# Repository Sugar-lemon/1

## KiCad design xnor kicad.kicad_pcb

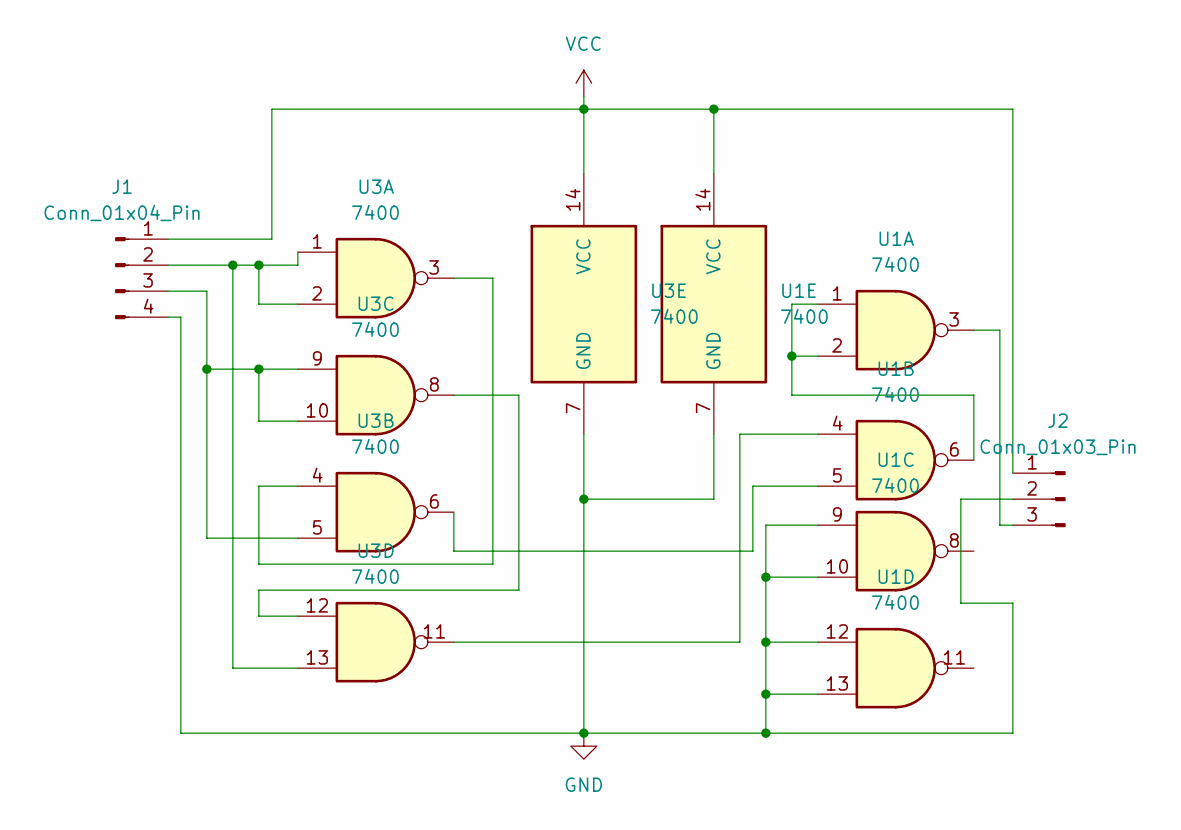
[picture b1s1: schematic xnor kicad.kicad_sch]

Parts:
J1: Conn_01x04_Pin
J2: Conn_01x03_Pin
U1, U3: 7400; DIP-14_W7.62mm

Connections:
GND: J1.4, J2.2, U1.7 (GND), U1.9, U1.10, U1.12, U1.13, U3.7 (GND)
unnamed: J1.2, U3.1, U3.2, U3.13
unnamed: J1.3, U3.5, U3.9, U3.10
unnamed: J2.3, U1.3
unnamed: U1.1, U1.2, U1.6
unnamed: U1.4, U3.11
unnamed: U1.5, U3.6
unnamed: U3.3, U3.4
unnamed: U3.8, U3.12
VCC: J1.1, J2.1, U1.14 (VCC), U3.14 (VCC)

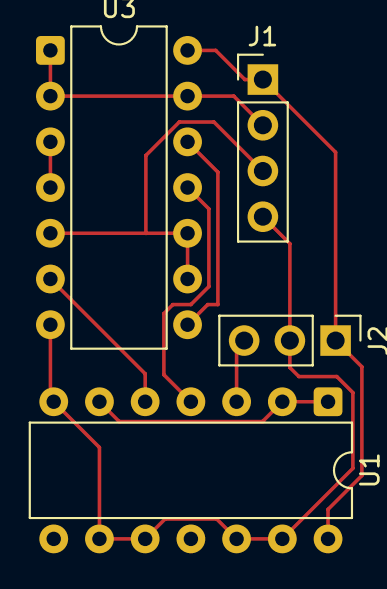
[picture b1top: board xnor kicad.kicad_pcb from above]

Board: 2 copper layers, 4 parts (0 on the bottom side), 10 nets.

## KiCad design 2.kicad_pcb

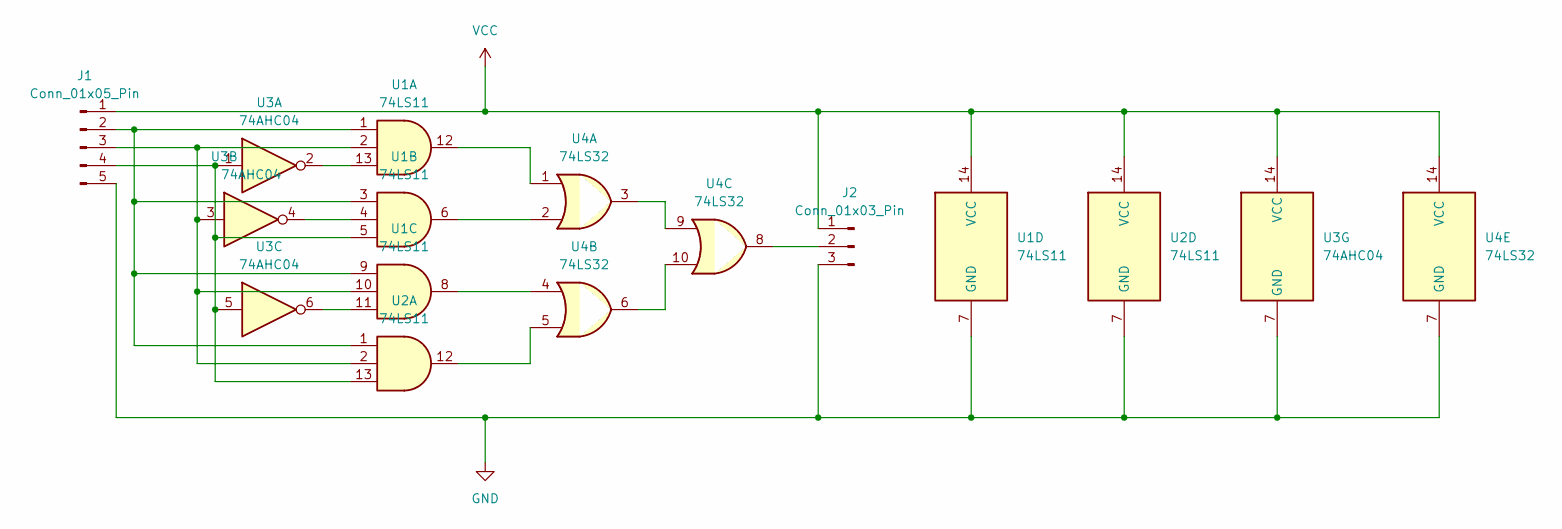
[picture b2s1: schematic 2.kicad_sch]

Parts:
J1: Conn_01x05_Pin; Wuerth_WR-WTB_64800511622_1x05_P1.50mm_Vertical
J2: Conn_01x03_Pin; Wuerth_WR-WTB_64800311622_1x03_P1.50mm_Vertical
U1, U2: 74LS11; DIP-14_W7.62mm
U3: 74AHC04; DIP-14_W7.62mm
U4: 74LS32; DIP-14_W7.62mm

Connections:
GND: J1.5, J2.3, U1.7 (GND), U2.7 (GND), U3.7 (GND), U4.7 (GND)
unnamed: J1.2, U1.1, U1.3, U1.9, U2.1
unnamed: J1.3, U1.2, U1.10, U2.2, U3.3
unnamed: J1.4, U1.5, U2.13, U3.1, U3.5
unnamed: J2.2, U4.8
unnamed: U1.4, U3.4
unnamed: U1.6, U4.2
unnamed: U1.8, U4.4
unnamed: U1.11, U3.6
unnamed: U1.12, U4.1
unnamed: U1.13, U3.2
unnamed: U2.12, U4.5
unnamed: U4.3, U4.9
unnamed: U4.6, U4.10
VCC: J1.1, J2.1, U1.14 (VCC), U2.14 (VCC), U3.14 (VCC), U4.14 (VCC)

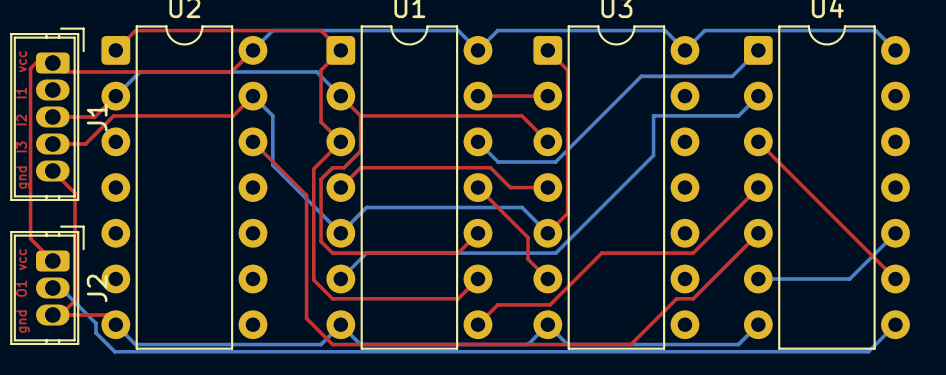
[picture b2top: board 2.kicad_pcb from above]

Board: 2 copper layers, 6 parts (0 on the bottom side), 15 nets.

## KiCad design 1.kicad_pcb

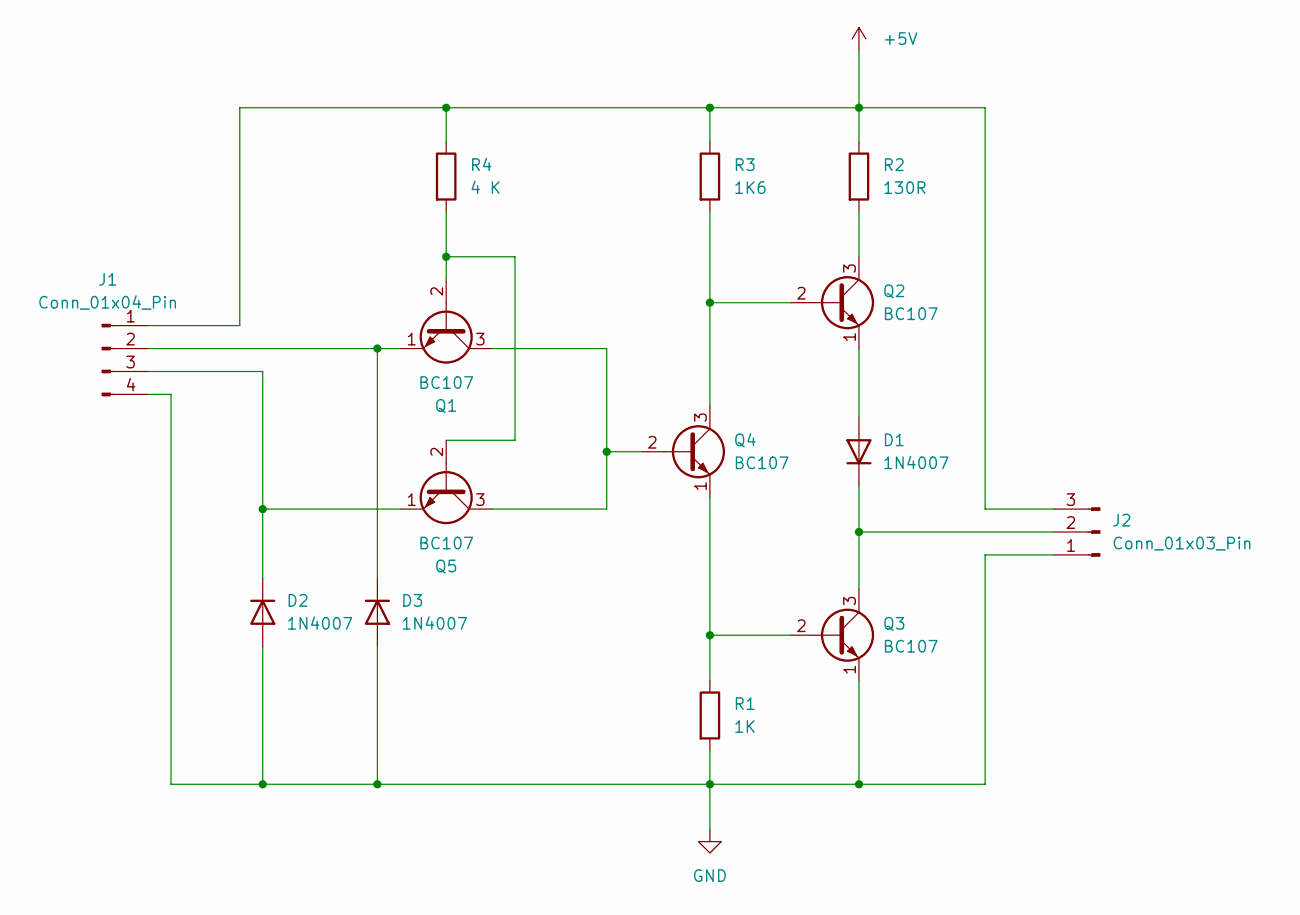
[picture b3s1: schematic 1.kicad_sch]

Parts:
D1, D2, D3: 1N4007; D_DO-41_SOD81_P10.16mm_Horizontal
J1: Conn_01x04_Pin; PinHeader_1x04_P2.54mm_Vertical
J2: Conn_01x03_Pin; PinHeader_1x03_P2.54mm_Vertical
Q1, Q2, Q3, Q4, Q5: BC107; TO-18-3
R1: 1K; R_Axial_DIN0207_L6.3mm_D2.5mm_P10.16mm_Horizontal
R2: 130R; R_Axial_DIN0207_L6.3mm_D2.5mm_P10.16mm_Horizontal
R3: 1K6; R_Axial_DIN0207_L6.3mm_D2.5mm_P10.16mm_Horizontal
R4: 4 K; R_Axial_DIN0207_L6.3mm_D2.5mm_P10.16mm_Horizontal

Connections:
+5V: J1.1, J2.3, R2.1, R3.1, R4.1
GND: D2.2 (A), D3.2 (A), J1.4, J2.1, Q3.1 (E), R1.2
unnamed: D1.2 (A), Q2.1 (E)
unnamed: D1.1 (K), J2.2, Q3.3 (C)
unnamed: D2.1 (K), J1.3, Q5.1 (E)
unnamed: D3.1 (K), J1.2, Q1.1 (E)
unnamed: Q1.2 (B), Q5.2 (B), R4.2
unnamed: Q1.3 (C), Q4.2 (B), Q5.3 (C)
unnamed: Q2.2 (B), Q4.3 (C), R3.2
unnamed: Q2.3 (C), R2.2
unnamed: Q3.2 (B), Q4.1 (E), R1.1

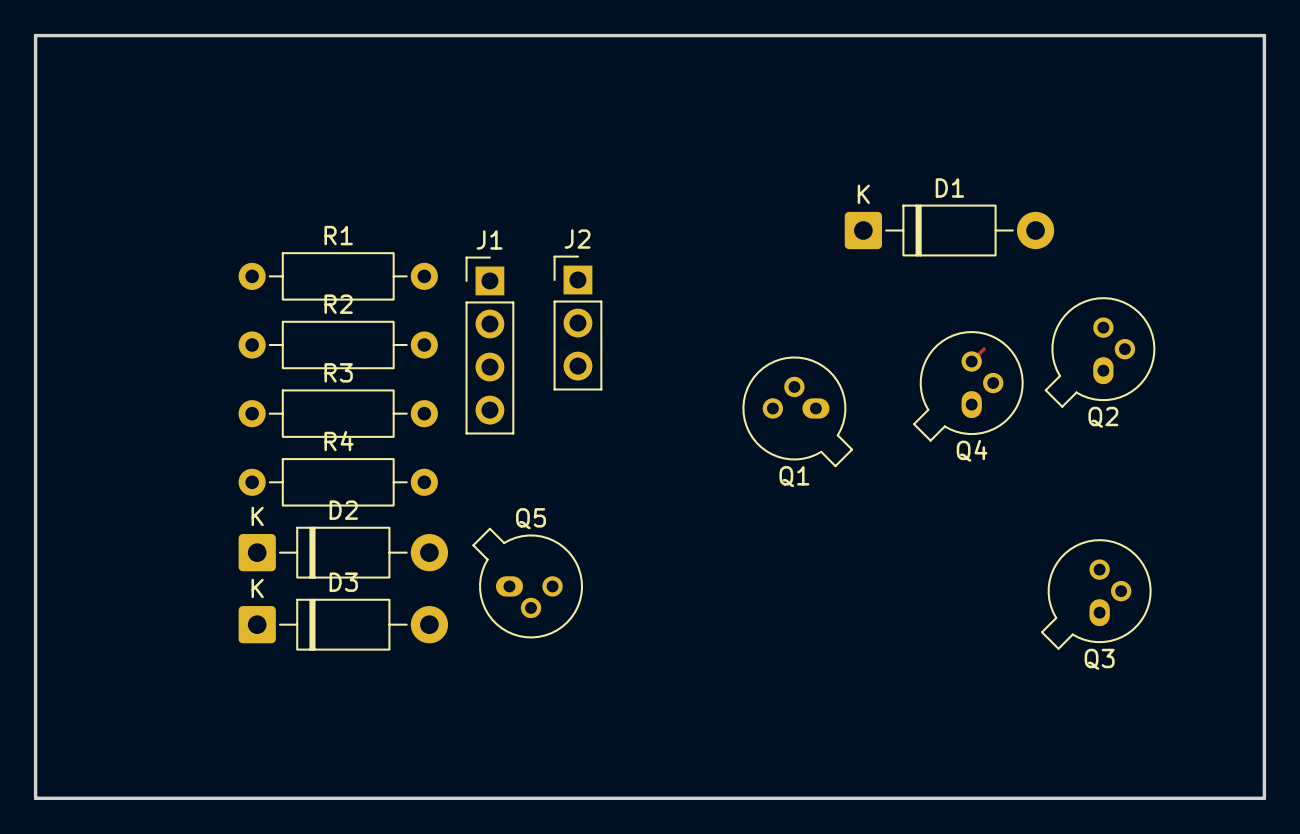
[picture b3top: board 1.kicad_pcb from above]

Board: 2 copper layers, 72.5 x 45.0 mm, 14 parts (0 on the bottom side), 11 nets.

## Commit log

2025-07-11 For practice
2025-07-11 1-create_basic_NAND_logic_discrete_gate: Create correct basic NAND gate schematic.
2025-07-11 1-create_basic_NAND_logic_discrete_gate: Added .gitignore.
2025-07-11 1-create_basic_NAND_logic_discrete_gate: Delete trash untracked files.
2025-07-11 1-create_basic_NAND_logic_discrete_gate: Delete trash resistors in 3d model.
2025-07-11 1-create_basic_NAND_logic_discrete_gate: Added board border.
2025-07-11 1-create_basic_NAND_logic_discrete_gate: Update .gitignore file.
2025-07-14 test
